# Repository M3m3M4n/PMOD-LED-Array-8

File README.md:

# PMOD LED Array 8

Small LED PMOD with 8 LEDS

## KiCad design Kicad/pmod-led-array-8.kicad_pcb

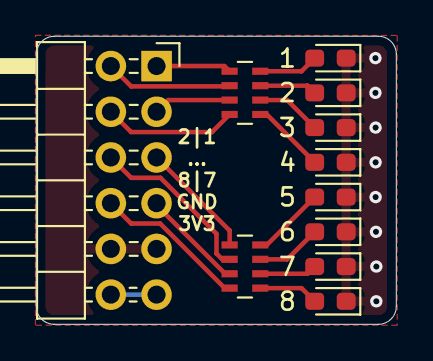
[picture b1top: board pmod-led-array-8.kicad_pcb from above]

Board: 2 copper layers, 20.0 x 16.0 mm, 11 parts (0 on the bottom side), 18 nets.

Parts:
1, 2, 3, 4, 5, 6, 7, 8: LED; LED_0603_1608Metric_Pad1.05x0.95mm_HandSolder
J1: PMOD; Pmod_Header_2x06_P2.54mm_Horizontal
R1, R2: 220; R_Array_Concave_4x0603

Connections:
+3V3: J1.6 (3.3V), J1.12 (3.3V)
/p1: J1.1, R1.5 (R4.2)
/p2: J1.7, R1.6 (R3.2)
/p3: J1.2, R1.7 (R2.2)
/p4: J1.8, R1.8 (R1.2)
/p5: J1.3, R2.5 (R4.2)
/p6: J1.9, R2.6 (R3.2)
/p7: J1.4, R2.7 (R2.2)
/p8: J1.10, R2.8 (R1.2)
GND: 1.1 (K), 2.1 (K), 3.1 (K), 4.1 (K), 5.1 (K), 6.1 (K), 7.1 (K), 8.1 (K), J1.5 (GND), J1.11 (GND)
unnamed: 1.2 (A), R1.1 (R1.1)
unnamed: 2.2 (A), R1.2 (R2.1)
unnamed: 3.2 (A), R1.3 (R3.1)
unnamed: 4.2 (A), R1.4 (R4.1)
unnamed: 5.2 (A), R2.1 (R1.1)
unnamed: 6.2 (A), R2.2 (R2.1)
unnamed: 7.2 (A), R2.3 (R3.1)
unnamed: 8.2 (A), R2.4 (R4.1)

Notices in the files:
Kicad/pmod-led-array-8.kicad_pcb:
CC-BY-SA
